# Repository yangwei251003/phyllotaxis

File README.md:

# PHYLLO · 声音生长成光

让声音沿着“向日葵”的黄金角排列变成光。PHYLLO把浏览器音频演示、STM32信号处理、144灯PCB与可拆卸外壳放在同一个工程中，共用一份几何与灯链数据，便于从画面追溯到代码和设计文件。

> 原项目保存的候选结构渲染，不是实板照片；电路、制造、接线、打印配合与实物性能仍待验证。

## 状态与功能

**开发中：采购前数字工程，软件可独立体验，硬件未实测。** 本次开源整理不启动EDA、不改变原设计、不制造或烧录。

- 浏览器演示黄金角阵列、三种空间灯效与配色；支持合成信号及本地音频分析。
- 固件核心实现去直流、Hann窗、512点FFT、RMS、七频段能量和谱通量节拍检测。
- STM32F411候选工程包含I2S DMA、音频队列、灯链映射、WS2812 DMA输出与串口遥测。
- PCB、原理图、可读电路图、参数化机械源与自有打印件模型可审阅。
- 网页设备区只读显示串口状态；浏览器动画不代表实体设备已正常工作。

## 技术栈

| 部分 | 技术与依赖 |
|---|---|
| 网页 | 原生JavaScript、Canvas、Web Audio、Web Serial；Node.js 18+用于本地服务/测试，无npm运行依赖 |
| 可移植核心 | C11、GCC、CMake 3.20+、Ninja、数学库 |
| 板级候选 | STM32F411CEU6、Arm GNU工具链、锁定ST HAL/CMSIS官方来源 |
| 电路 | 嘉立创EDA专业版原工程及KiCad审阅工程，另有PDF阅读图 |
| 结构 | Python参数化源、build123d/cadgen工作流；可直接查看已导出的自有STEP/STL/3MF |

## 快速体验网页

```powershell
git clone https://github.com/yangwei251003/phyllotaxis.git
cd phyllotaxis
node web/server.mjs
```

打开 `http://127.0.0.1:8765/`，默认合成信号即可体验，不需要麦克风或硬件。麦克风需要浏览器授权；音频在本地处理。Web Serial需要支持该API的浏览器和安全上下文，不能笼统承诺所有手机可用。

仓库配置了GitHub Pages静态发布工作流，启用后可从 [在线演示](https://yangwei251003.github.io/phyllotaxis/) 直接体验。网页展示与实体硬件验收是两件事。

## 测试可移植固件核心

需要GCC、CMake与Ninja已在PATH中：

```powershell
cmake -S firmware -B .runtime/host -G Ninja -DCMAKE_C_COMPILER=gcc
cmake --build .runtime/host
ctest --test-dir .runtime/host --output-on-failure
```

网页单元测试与本地HTTP检查：

```powershell
cd web
node --test tests/*.test.mjs
cd ..
python scripts/smoke-web.py
```

## 可选：离线构建F411候选

需要Git、Python 3、CMake、Ninja及 `arm-none-eabi-gcc/objcopy/nm/size` 在PATH：

```powershell
python firmware/bootstrap_sources.py
python firmware/build_candidate.py
```

bootstrap只下载锁定版本的官方源码并检查提交/哈希，遇到本地修改会停止，不重置源码。供应商目录和编译输出已忽略。此命令不连接、枚举、烧录或操作开发板；候选输出不构成烧录放行。真实板型、麦克风槽位、数据时序、供电、温升和灯链需要后续实物核实。

## 设计文件与目录

```text
web/                      网页演示与遥测解析
firmware/include,src,tests 可移植C核心与测试
firmware/platform/        F411候选板级工程
shared/                   网页、PCB和结构共用几何/灯链数据
hardware/eda/             嘉立创原设计源
hardware/prototype-v02/    后续候选KiCad工程、PDF和制造审阅资料
mechanical/               自有参数源及独立零件STEP/STL/3MF
docs/images/              原项目保存的真实界面/渲染图
```

制造目录名称中的REVIEW和NOT-FOR-MANUFACTURE保留原意；未在本次开源整理复跑DRC/ERC或重新核对EDA连接。第三方参考板/麦克风模型及包含它们的完整装配模型未再分发，详见 [来源与排除范围](PROVENANCE.md)。独立零件可直接查看，但不能据数字模型宣称打印配合通过。

## 验证、规划与许可

本次实际执行结果见 [VALIDATION.md](VALIDATION.md)，历史检查不能自动升级为当前实板结论。更新与规划见 [CHANGELOG.md](CHANGELOG.md)。自有部分按 [MIT](LICENSE) 发布；外部依赖及厂商参考的许可边界见 [THIRD_PARTY_NOTICES.md](THIRD_PARTY_NOTICES.md)。

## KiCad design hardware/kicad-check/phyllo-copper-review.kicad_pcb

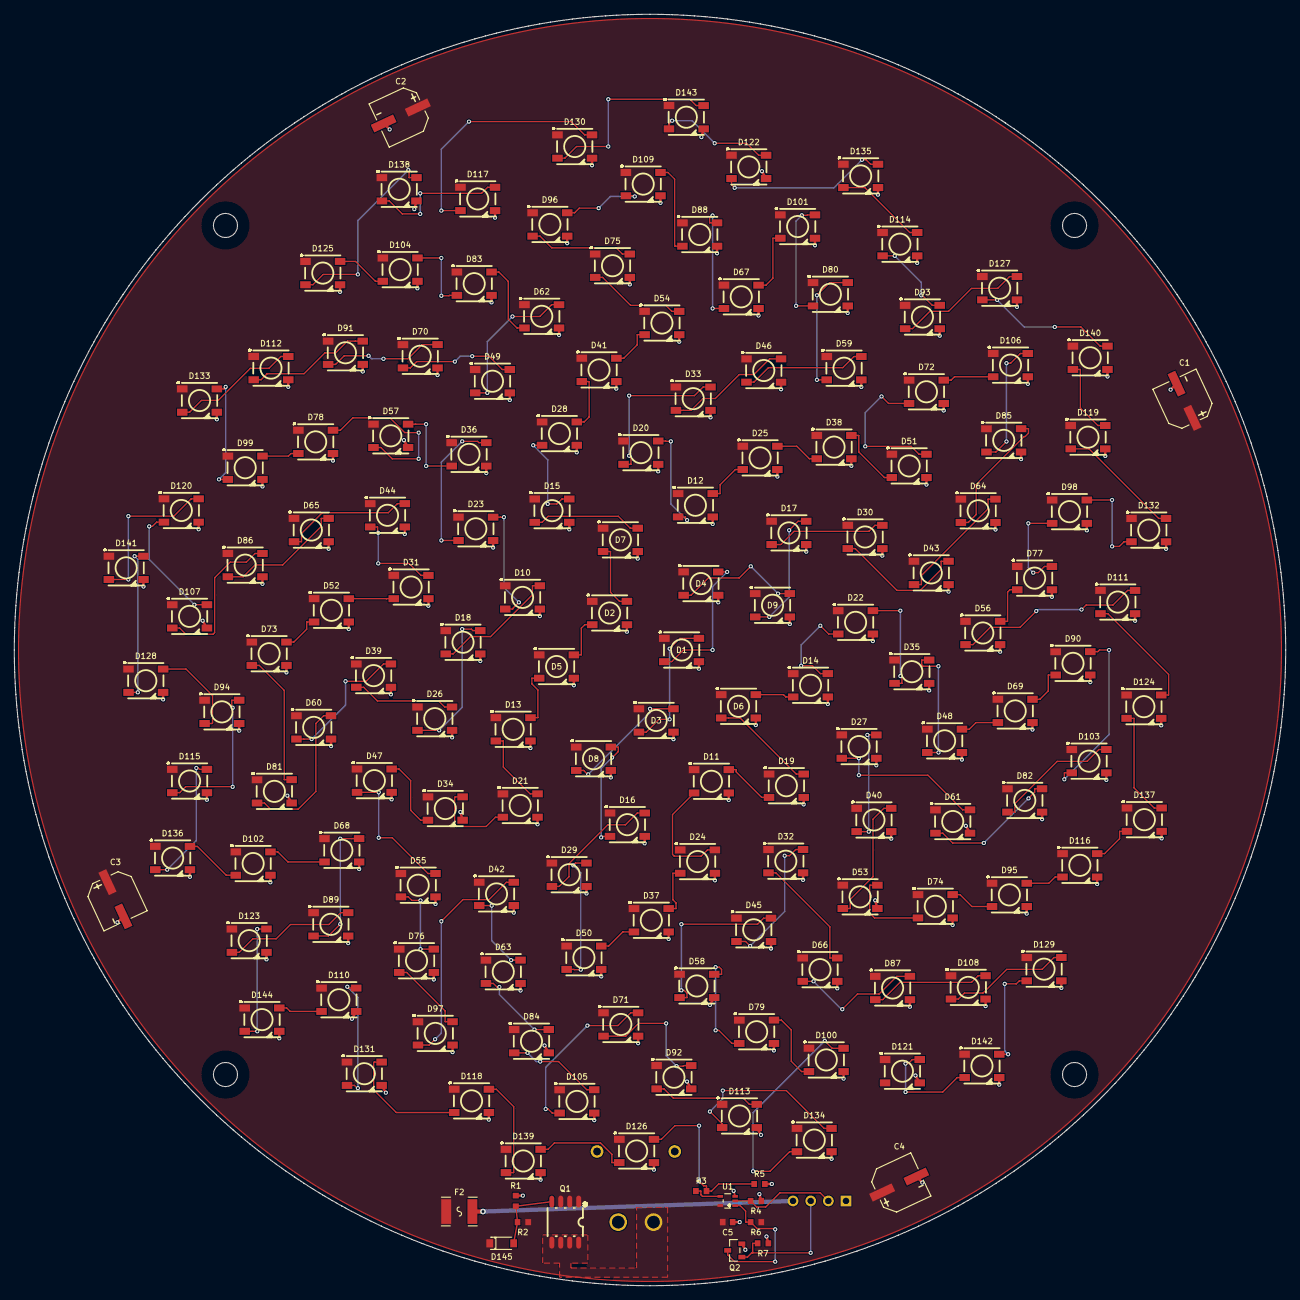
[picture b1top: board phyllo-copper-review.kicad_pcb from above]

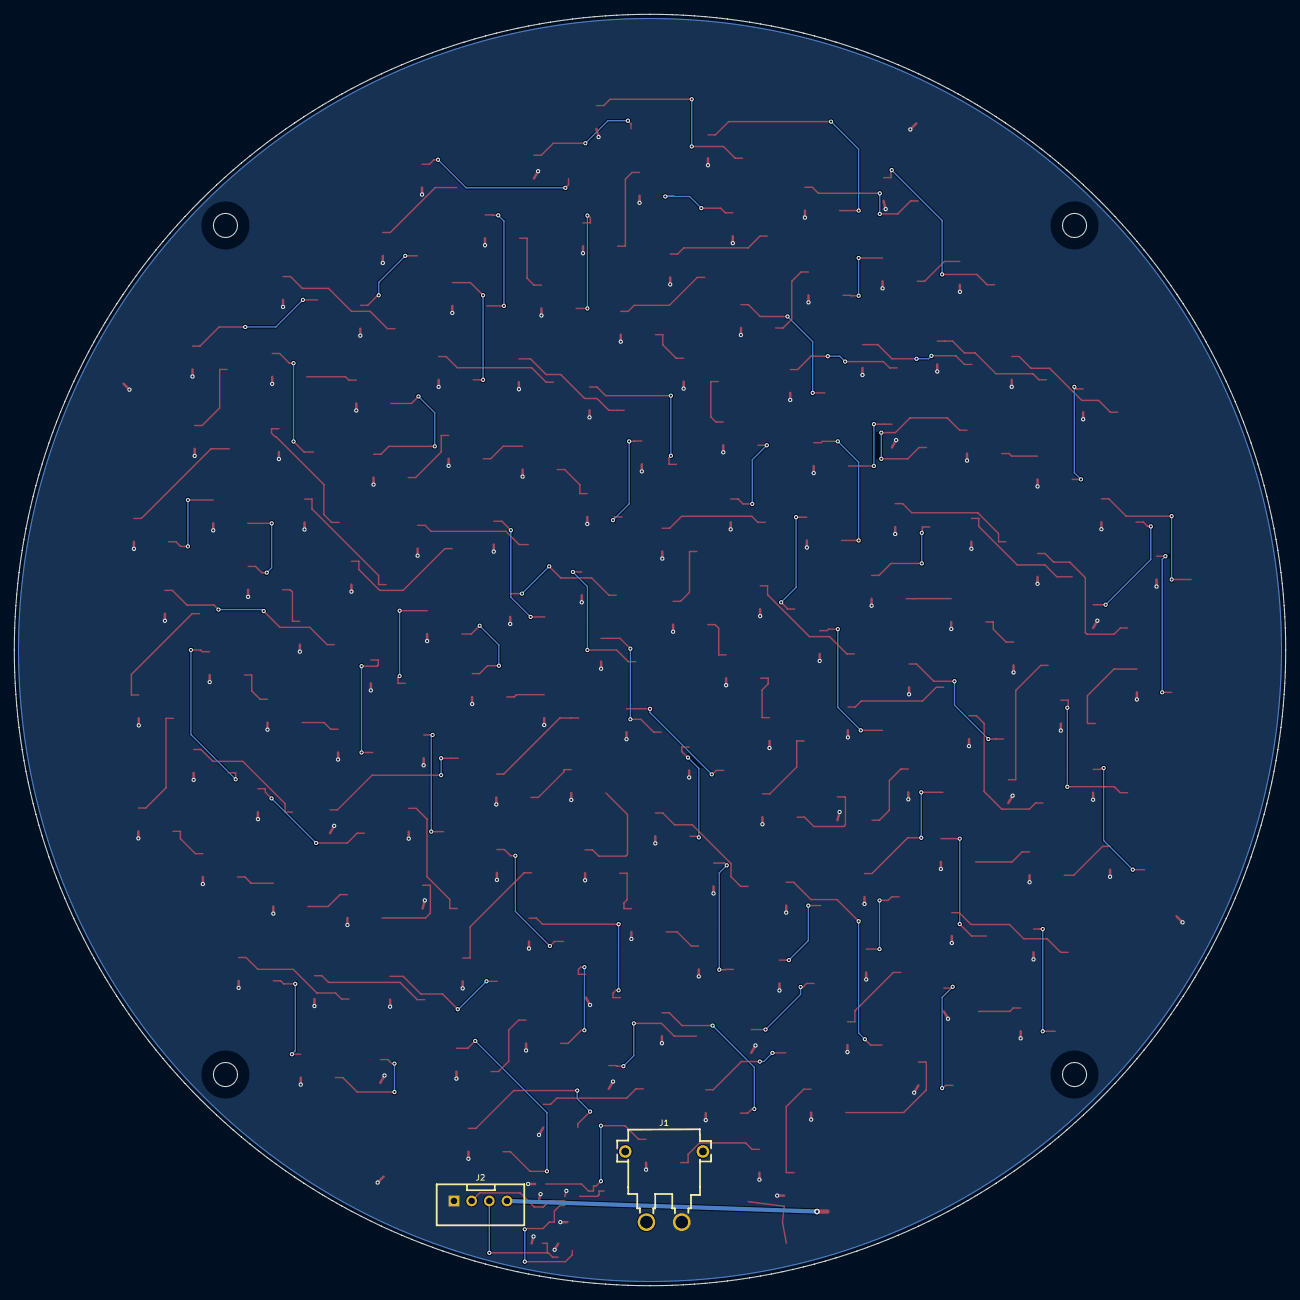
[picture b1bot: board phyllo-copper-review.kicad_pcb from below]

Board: 2 copper layers, 180.0 x 180.0 mm, 167 parts (2 on the bottom side), 153 nets.

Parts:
C1, C2, C3, C4: MA10V470M6X8; C46550459
C5: CC0603KRX7R9BB104; C14663
D1, D2, D3, D4, D5, D6, D7, D8, D9, D10, D11, D12, D13, D14, D15, D16, D17, D18, D19, D20, D21, D22, D23, D24, D25, D26, D27, D28, D29, D30, D31, D32, D33, D34, D35, D36, D37, D38, D39, D40, D41, D42, D43, D44, D45, D46, D47, D48, D49, D50, D51, D52, D53, D54, D55, D56, D57, D58, D59, D60, D61, D62, D63, D64, D65, D66, D67, D68, D69, D70, D71, D72, D73, D74, D75, D76, D77, D78, D79, D80, D81, D82, D83, D84, D85, D86, D87, D88, D89, D90, D91, D92, D93, D94, D95, D96, D97, D98, D99, D100, D101, D102, D103, D104, D105, D106, D107, D108, D109, D110, D111, D112, D113, D114, D115, D116, D117, D118, D119, D120, D121, D122, D123, D124, D125, D126, D127, D128, D129, D130, D131, D132, D133, D134, D135, D136, D137, D138, D139, D140, D141, D142, D143, D144: WS2812B-B-V6; C52941391
D145: BZT52C12; C271259
F2: MF-MSMF050-2; C17313
J1: XT30PW-M30.G.Y; C431092
J2: B4B-XH-A-G; C594232
Q1: CJQ16P03; C2910138
Q2: 2N7002; C8545
R1: 0603WAF1001T5E; C21190
R2: 0603WAF1004T5E; C22935
R3: 0603WAF3300T5E; C23138
R4, R5, R6, R7: 0603WAF1003T5E; C25803
U1: 74AHCT1G125GW,125; C12495
mount-1, mount-2, mount-3, mount-4: NPTH_3.4mm

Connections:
5V_LED: C1.1, C2.1, C3.1, C4.1, C5.1, D1.1, D2.1, D3.1, D4.1, D5.1, D6.1, D7.1, D8.1, D9.1, D10.1, D11.1, D12.1, D13.1, D14.1, D15.1, D16.1, D17.1, D18.1, D19.1, D20.1, D21.1, D22.1, D23.1, D24.1, D25.1, D26.1, D27.1, D28.1, D29.1, D30.1, D31.1, D32.1, D33.1, D34.1, D35.1, D36.1, D37.1, D38.1, D39.1, D40.1, D41.1, D42.1, D43.1, D44.1, D45.1, D46.1, D47.1, D48.1, D49.1, D50.1, D51.1, D52.1, D53.1, D54.1, D55.1, D56.1, D57.1, D58.1, D59.1, D60.1, D61.1, D62.1, D63.1, D64.1, D65.1, D66.1, D67.1, D68.1, D69.1, D70.1, D71.1, D72.1, D73.1, D74.1, D75.1, D76.1, D77.1, D78.1, D79.1, D80.1, D81.1, D82.1, D83.1, D84.1, D85.1, D86.1, D87.1, D88.1, D89.1, D90.1, D91.1, D92.1, D93.1, D94.1, D95.1, D96.1, D97.1, D98.1, D99.1, D100.1, D101.1, D102.1, D103.1, D104.1, D105.1, D106.1, D107.1, D108.1, D109.1, D110.1, D111.1, D112.1, D113.1, D114.1, D115.1, D116.1, D117.1, D118.1, D119.1, D120.1, D121.1, D122.1, D123.1, D124.1, D125.1, D126.1, D127.1, D128.1, D129.1, D130.1, D131.1, D132.1, D133.1, D134.1, D135.1, D136.1, D137.1, D138.1, D139.1, D140.1, D141.1, D142.1, D143.1, D144.1, D145.1, F2.1, Q1.1, Q1.2, Q1.3, R2.2, R6.2, U1.5
5V_MCU: F2.2, J2.4
DATA_001: D126.2, D139.4
DATA_002: D118.4, D139.2
DATA_003: D118.2, D131.4
DATA_3V3: J2.2, R4.1, U1.2
DATA_004: D110.4, D131.2
DATA_005: D110.2, D144.4
DATA_006: D123.4, D144.2
DATA_007: D89.4, D123.2
DATA_008: D68.4, D89.2
DATA_009: D68.2, D102.4
DATA_010: D102.2, D136.4
DATA_011: D115.4, D136.2
DATA_012: D94.4, D115.2
DATA_013: D94.2, D128.4
DATA_014: D128.2, D141.4
DATA_015: D120.4, D141.2
DATA_016: D107.4, D120.2
DATA_017: D86.4, D107.2
DATA_018: D65.4, D86.2
DATA_019: D44.4, D65.2
DATA_020: D31.4, D44.2
DATA_021: D31.2, D52.4
DATA_022: D52.2, D73.4
DATA_023: D73.2, D81.4
DATA_024: D60.4, D81.2
DATA_025: D39.4, D60.2
DATA_026: D26.4, D39.2
DATA_027: D18.4, D26.2
DATA_028: D10.4, D18.2
DATA_029: D10.2, D23.4
DATA_030: D23.2, D36.4
DATA_031: D36.2, D57.4
DATA_032: D57.2, D78.4
DATA_033: D78.2, D99.4
DATA_034: D99.2, D133.4
DATA_035: D112.4, D133.2
DATA_036: D91.4, D112.2
DATA_037: D70.4, D91.2
DATA_038: D49.4, D70.2
DATA_039: D49.2, D62.4
DATA_040: D62.2, D83.4
DATA_041: D83.2, D104.4
DATA_042: D104.2, D125.4
DATA_043: D125.2, D138.4
DATA_044: D117.4, D138.2
DATA_045: D117.2, D130.4
DATA_046: D130.2, D143.4
DATA_047: D122.4, D143.2
DATA_048: D122.2, D135.4
DATA_049: D114.4, D135.2
DATA_050: D93.4, D114.2
DATA_051: D93.2, D127.4
DATA_052: D127.2, D140.4
DATA_053: D119.4, D140.2
DATA_054: D119.2, D132.4
DATA_055: D98.4, D132.2
DATA_056: D77.4, D98.2
DATA_057: D56.4, D77.2
DATA_058: D56.2, D111.4
DATA_059: D111.2, D124.4
DATA_060: D124.2, D137.4
DATA_061: D116.4, D137.2
DATA_062: D95.4, D116.2
DATA_063: D74.4, D95.2
DATA_064: D53.4, D74.2
DATA_065: D40.4, D53.2
DATA_066: D27.4, D40.2
DATA_067: D27.2, D61.4
DATA_068: D61.2, D82.4
DATA_069: D82.2, D103.4
DATA_070: D90.4, D103.2
DATA_071: D69.4, D90.2
DATA_072: D48.4, D69.2
DATA_073: D35.4, D48.2
DATA_074: D22.4, D35.2
DATA_075: D14.4, D22.2
DATA_076: D6.4, D14.2
DATA_077: D6.2, D19.4
DATA_078: D11.4, D19.2
DATA_079: D11.2, D24.4
DATA_080: D24.2, D37.4
DATA_081: D37.2, D50.4
DATA_082: D29.4, D50.2
DATA_083: D16.4, D29.2
DATA_084: D8.4, D16.2
DATA_085: D3.4, D8.2
DATA_086: D1.4, D3.2
DATA_087: D1.2, D4.4
DATA_088: D4.2, D9.4
DATA_089: D9.2, D17.4
DATA_090: D17.2, D30.4
DATA_091: D30.2, D43.4
DATA_092: D43.2, D64.4
DATA_093: D64.2, D85.4
DATA_094: D85.2, D106.4
DATA_095: D72.4, D106.2
DATA_096: D51.4, D72.2
DATA_097: D38.4, D51.2
DATA_098: D25.4, D38.2
DATA_099: D12.4, D25.2
DATA_100: D12.2, D20.4
DATA_101: D20.2, D33.4
DATA_102: D33.2, D46.4
DATA_103: D46.2, D59.4
DATA_104: D59.2, D80.4
DATA_105: D80.2, D101.4
DATA_106: D67.4, D101.2
DATA_107: D67.2, D88.4
DATA_108: D88.2, D109.4
DATA_109: D96.4, D109.2
DATA_110: D75.4, D96.2
DATA_111: D54.4, D75.2
DATA_112: D41.4, D54.2
DATA_113: D28.4, D41.2
DATA_114: D15.4, D28.2
DATA_115: D7.4, D15.2
DATA_116: D2.4, D7.2
DATA_117: D2.2, D5.4
DATA_118: D5.2, D13.4
DATA_119: D13.2, D21.4
DATA_120: D21.2, D34.4
DATA_121: D34.2, D47.4
DATA_122: D47.2, D55.4
DATA_123: D55.2, D76.4
DATA_124: D76.2, D97.4
DATA_125: D42.4, D97.2
DATA_126: D42.2, D63.4
DATA_127: D63.2, D84.4
DATA_128: D84.2, D105.4
DATA_129: D71.4, D105.2
DATA_130: D71.2, D92.4
DATA_131: D92.2, D113.4
DATA_132: D113.2, D134.4
DATA_133: D100.4, D134.2
DATA_134: D79.4, D100.2
DATA_135: D58.4, D79.2
DATA_136: D45.4, D58.2
DATA_137: D32.4, D45.2
DATA_138: D32.2, D66.4
DATA_139: D66.2, D87.4
DATA_140: D87.2, D108.4
DATA_141: D108.2, D129.4
DATA_142: D129.2, D142.4
DATA_143: D121.4, D142.2
DATA_BUFFERED: R3.1, U1.4
DATA_OE_N: Q2.3, R6.1, U1.1
ENABLE_3V3: J2.3, Q2.1, R7.1
GND: C1.2, C2.2, C3.2, C4.2, C5.2, D1.3, D2.3, D3.3, D4.3, D5.3, D6.3, D7.3, D8.3, D9.3, D10.3, D11.3, D12.3, D13.3, D14.3, D15.3, D16.3, D17.3, D18.3, D19.3, D20.3, D21.3, D22.3, D23.3, D24.3, D25.3, D26.3, D27.3, D28.3, D29.3, D30.3, D31.3, D32.3, D33.3, D34.3, D35.3, D36.3, D37.3, D38.3, D39.3, D40.3, D41.3, D42.3, D43.3, D44.3, D45.3, D46.3, D47.3, D48.3, D49.3, D50.3, D51.3, D52.3, D53.3, D54.3, D55.3, D56.3, D57.3, D58.3, D59.3, D60.3, D61.3, D62.3, D63.3, D64.3, D65.3, D66.3, D67.3, D68.3, D69.3, D70.3, D71.3, D72.3, D73.3, D74.3, D75.3, D76.3, D77.3, D78.3, D79.3, D80.3, D81.3, D82.3, D83.3, D84.3, D85.3, D86.3, D87.3, D88.3, D89.3, D90.3, D91.3, D92.3, D93.3, D94.3, D95.3, D96.3, D97.3, D98.3, D99.3, D100.3, D101.3, D102.3, D103.3, D104.3, D105.3, D106.3, D107.3, D108.3, D109.3, D110.3, D111.3, D112.3, D113.3, D114.3, D115.3, D116.3, D117.3, D118.3, D119.3, D120.3, D121.3, D122.3, D123.3, D124.3, D125.3, D126.3, D127.3, D128.3, D129.3, D130.3, D131.3, D132.3, D133.3, D134.3, D135.3, D136.3, D137.3, D138.3, D139.3, D140.3, D141.3, D142.3, D143.3, D144.3, J1.1, J2.1, Q2.2, R1.2, R4.2, R5.2, R7.2, U1.3
LED_DATA_IN: D126.4, R3.2, R5.1
PMOS_GATE: D145.2, Q1.4, R1.1, R2.1
VIN_FUSED: J1.2, Q1.5, Q1.6, Q1.7, Q1.8

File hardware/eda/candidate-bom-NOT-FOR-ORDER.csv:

Status,Designator,Quantity,Manufacturer,Manufacturer Part,Footprint,LCSC Part,Assembly class from library
DRAFT / no PCB parity,U1,1,Nexperia(安世),"74AHCT1G125GW,125",SOT-353,C12495,Extended Part
DRAFT / no PCB parity,C5,1,YAGEO(国巨),CC0603KRX7R9BB104,0603,C14663,Basic Part
DRAFT / no PCB parity,F2,1,BOURNS,MF-MSMF050-2,1812,C17313,Extended Part
DRAFT / no PCB parity,R1,1,UNI-ROYAL(厚声),0603WAF1001T5E,0603,C21190,Basic Part
DRAFT / no PCB parity,R2,1,UNI-ROYAL(厚声),0603WAF1004T5E,0603,C22935,Basic Part
DRAFT / no PCB parity,R3,1,UNI-ROYAL(厚声),0603WAF3300T5E,0603,C23138,Basic Part
DRAFT / no PCB parity,"R4,R5,R6,R7",4,UNI-ROYAL(厚声),0603WAF1003T5E,0603,C25803,Basic Part
DRAFT / no PCB parity,D145,1,BORN(伯恩半导体),BZT52C12,SOD-123,C271259,Extended Part
DRAFT / no PCB parity,Q1,1,CJ(江苏长电/长晶),CJQ16P03,SOP-8,C2910138,Extended Part
DRAFT / no PCB parity,J1,1,AMASS(艾迈斯),XT30PW-M30.G.Y,-,C431092,Extended Part
DRAFT / no PCB parity,"C1,C2,C3,C4",4,JIERR(捷而瑞),MA10V470M6X8,"SMD,D6.3xL7.7mm",C46550459,Extended Part
DRAFT / no PCB parity,"D1,D2,D3,D4,D5,D6,D7,D8,D9,D10,D11,D12,D13,D14,D15,D16,D17,D18,D19,D20,D21,D22,D23,D24,D25,D26,D27,D28,D29,D30,D31,D32,D33,D34,D35,D36,D37,D38,D39,D40,D41,D42,D43,D44,D45,D46,D47,D48,D49,D50,D51,D52,D53,D54,D55,D56,D57,D58,D59,D60,D61,D62,D63,D64,D65,D66,D67,D68,D69,D70,D71,D72,D73,D74,D75,D76,D77,D78,D79,D80,D81,D82,D83,D84,D85,D86,D87,D88,D89,D90,D91,D92,D93,D94,D95,D96,D97,D98,D99,D100,D101,D102,D103,D104,D105,D106,D107,D108,D109,D110,D111,D112,D113,D114,D115,D116,D117,D118,D119,D120,D121,D122,D123,D124,D125,D126,D127,D128,D129,D130,D131,D132,D133,D134,D135,D136,D137,D138,D139,D140,D141,D142,D143,D144",144,worldsemi,WS2812B-B-V6,SMD5050-4P,C52941391,Extended Part
DRAFT / no PCB parity,J2,1,JST,B4B-XH-A-G,"插件,P=2.5mm",C594232,Extended Part
DRAFT / no PCB parity,Q2,1,CJ(江苏长电/长晶),2N7002,SOT-23,C8545,Basic Part

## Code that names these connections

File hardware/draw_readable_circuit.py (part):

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# Sheet 1: reverse-polarity and reservoir network.
p=page('供电与反接保护','从已保存的原生网表逐脚核对；相同网络名代表电气连接，框内为功能说明。')
box(p,95,220,155,185,'J1  XT30','C431092')
pin(p,'J1',[2],'VIN_FUSED',250,280,dx=-70,dy=35,extra='+')
pin(p,'J1',[1],'GND',250,365,dx=-70,extra='−')
pin(p,'J1',[3,4],None,150,405,dy=28,extra='NC')
text(p,95,468,'3/4 辅助脚独立悬空',16,MUTED)
text(p,95,495,'非正负电源端',16,MUTED)
wire(p,'VIN_FUSED',(250,280),(520,280));label(p,285,270,'VIN_FUSED')
box(p,520,220,240,125,'Q1  CJQ16P03','PMOS 反接保护')
pin(p,'Q1',[5,6,7,8],'VIN_FUSED',520,280,dx=13,dy=44,extra='D')
pin(p,'Q1',[1,2,3],'5V_LED',760,280,dx=-105,dy=44,extra='S')
pin(p,'Q1',[4],'PMOS_GATE',625,345,dx=12,dy=25,extra='G')
wire(p,'5V_LED',(760,280),(1460,280));label(p,1280,265,'5V_LED')
wire(p,'PMOS_GATE',(625,345),(625,435),(1025,435));label(p,650,430,'PMOS_GATE')
resistor(p,'R2','1M',850,335,True,2,1,'5V_LED','PMOS_GATE')
wire(p,'5V_LED',(850,280),(850,335));dot(p,850,280)
wire(p,'PMOS_GATE',(850,400),(850,435));dot(p,850,435)
# Explicit anode/cathode representation avoids ambiguous zener symbol polarity.
box(p,980,325,95,85,'D145','12V ZD')
pin(p,'D145',[1],'5V_LED',1025,325,dx=58,dy=9,extra='K')
pin(p,'D145',[2],'PMOS_GATE',1025,410,dx=58,dy=0,extra='A')
wire(p,'5V_LED',(1025,280),(1025,325));dot(p,1025,280)
wire(p,'PMOS_GATE',(1025,410),(1025,435))
resistor(p,'R1','1k',625,495,True,1,2,'PMOS_GATE','GND')
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wire(p,'5V_MCU',(250,260),(380,260));label(p,280,250,'5V_MCU')
wire(p,'GND',(250,390),(305,390),(305,510),(345,510));label(p,290,545,'GND')
box(p,680,260,190,190,'U1','74AHCT1G125GW')
pin(p,'U1',[2],'DATA_3V3',680,330,dx=12,dy=25,extra='A')
pin(p,'U1',[4],'DATA_BUFFERED',870,330,dx=-55,dy=25,extra='Y')
pin(p,'U1',[5],'5V_LED',775,260,dx=12,extra='VCC')
pin(p,'U1',[3],'GND',775,450,dx=10,dy=-10,extra='GND')
pin(p,'U1',[1],'DATA_OE_N',680,410,dx=12,dy=12,extra='/OE')
wire(p,'DATA_3V3',(250,330),(680,330));label(p,415,320,'DATA_3V3')
wire(p,'5V_LED',(775,260),(775,175),(975,175));label(p,800,168,'5V_LED')
wire(p,'GND',(775,450),(775,485),(825,485));label(p,800,515,'GND')
capacitor(p,'C5','100nF',975,220,False)
wire(p,'5V_LED',(975,175),(975,220))
wire(p,'GND',(975,236),(975,260),(1030,260));label(p,1010,245,'GND')
wire(p,'DATA_BUFFERED',(870,330),(1060,330));label(p,881,380,'DATA_BUFFERED')
resistor(p,'R3','330Ω',1060,330,False,1,2,'DATA_BUFFERED','LED_DATA_IN')
wire(p,'LED_DATA_IN',(1150,330),(1480,330));label(p,1235,320,'LED_DATA_IN')
text(p,1230,375,'至原生灯链的首灯DIN',17)
resistor(p,'R4','100k',450,455,True,1,2,'DATA_3V3','GND')
wire(p,'DATA_3V3',(450,330),(450,455));dot(p,450,330)
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wire(p,'LED_DATA_IN',(1370,330),(1370,455));dot(p,1370,330)
wire(p,'GND',(1370,520),(1370,605),(1450,605));label(p,1405,595,'GND')
wire(p,'DATA_OE_N',(680,410),(630,410),(630,560),(1060,560))
label(p,775,550,'DATA_OE_N')
resistor(p,'R6','100k',1060,435,True,2,1,'5V_LED','DATA_OE_N')
wire(p,'5V_LED',(1060,435),(1060,406),(1150,406));label(p,1100,398,'5V_LED')
wire(p,'DATA_OE_N',(1060,500),(1060,560))
box(p,605,655,185,120,'Q2  2N7002','NMOS使能下拉')
pin(p,'Q2',[3],'DATA_OE_N',695,655,dx=12,extra='D')
pin(p,'Q2',[1],'ENABLE_3V3',605,735,dx=12,dy=23,extra='G')
pin(p,'Q2',[2],'GND',695,775,dx=12,dy=-10,extra='S')
wire(p,'DATA_OE_N',(695,560),(695,655));dot(p,695,560)
wire(p,'ENABLE_3V3',(250,435),(375,435),(375,735),(605,735));label(p,385,713,'ENABLE_3V3')
resistor(p,'R7','100k',470,790,True,1,2,'ENABLE_3V3','GND')
wire(p,'ENABLE_3V3',(470,735),(470,790));dot(p,470,735)
wire(p,'GND',(470,855),(470,900),(695,900),(695,775));label(p,605,893,'GND')
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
